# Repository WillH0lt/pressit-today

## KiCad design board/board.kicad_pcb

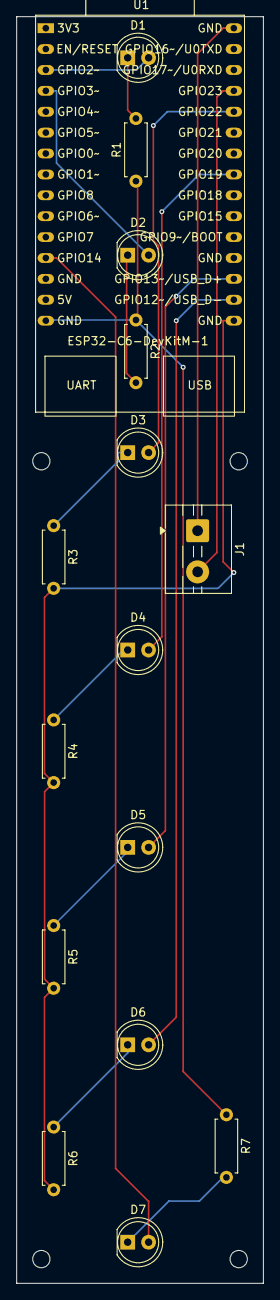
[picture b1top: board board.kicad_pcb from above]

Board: 2 copper layers, 30.0 x 154.0 mm, 16 parts (0 on the bottom side), 18 nets.

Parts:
D1, D2, D3, D4, D5, D6, D7: LED; LED_D5.0mm
J1: Screw_Terminal_01x02; TerminalBlock_MaiXu_MX126-5.0-02P_1x02_P5.00mm
R1, R2, R3, R4, R5, R6, R7: 100R; R_Axial_DIN0207_L6.3mm_D2.5mm_P7.62mm_Horizontal
U1: ESP32-C6-DevKitM-1

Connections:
unnamed: D1.2 (A), U1.3 (GPIO2)
unnamed: D1.1 (K), R1.2
unnamed: D2.2 (A), U1.4 (GPIO3)
unnamed: D2.1 (K), R2.2
unnamed: D3.2 (A), U1.26 (GPIO22)
unnamed: D3.1 (K), R3.1
unnamed: D4.2 (A), U1.23 (GPIO19)
unnamed: D4.1 (K), R4.1
unnamed: D5.2 (A), U1.18 (GPIO13/USB_D+)
unnamed: D5.1 (K), R5.1
unnamed: D6.2 (A), U1.17 (GPIO12/USB_D-)
unnamed: D6.1 (K), R6.1
unnamed: D7.2 (A), U1.12 (GPIO14)
unnamed: D7.1 (K), R7.2
unnamed: J1.1, U1.30 (GND)
unnamed: J1.2, U1.27 (GPIO23)
unnamed: R1.1, R2.1, R7.1, U1.15 (GND)
unnamed: R3.2, R4.2, R5.2, R6.2, U1.16 (GND)

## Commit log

2025-12-15 stats
2025-12-20 cleaning up ui
2026-01-01 finishing touches
2026-01-04 board design
2026-01-04 use local time
2026-01-04 timezone dst
2026-01-11 Enhance timezone handling and NTP synchronization logic
2026-01-16 fixes
2026-02-07 board
2026-02-16 branding
